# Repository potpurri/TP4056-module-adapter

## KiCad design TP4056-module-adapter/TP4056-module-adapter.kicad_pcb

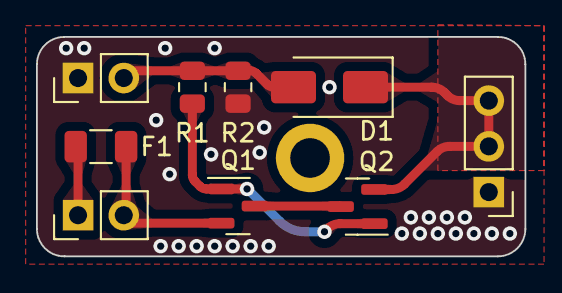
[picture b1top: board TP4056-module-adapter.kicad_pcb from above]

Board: 2 copper layers, 27.1 x 12.2 mm, 10 parts (0 on the bottom side), 7 nets.

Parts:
D1: SS34; D_SMA
F1: 1.5A; Fuse_1206_3216Metric
H1: MountingHole; MountingHole_2.2mm_M2_DIN965_Pad
J1, J2: Conn_01x02; PinHeader_1x02_P2.54mm_Vertical
J3: Conn_01x03; PinHeader_1x03_P2.54mm_Vertical
Q1, Q2: SI2301; SOT-23
R1: 1k; R_0805_2012Metric
R2: 10k; R_0805_2012Metric

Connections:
+BATT: F1.1, J2.1
GND: J1.1, J3.1, R2.2
LINE: F1.2, J2.2, Q1.2 (S)
unnamed: Q1.3 (D), Q2.3 (D)
unnamed: Q1.1 (G), Q2.1 (G), R1.1
VBUS: D1.2 (A), J1.2, R1.2, R2.1
VCC: D1.1 (K), J3.2, J3.3, Q2.2 (S)

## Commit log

2024-11-24 board layout
2024-11-27 layout update
2024-12-11 v1.2 - ready for ordering
2024-12-27 updated wrong pmos in schematic
